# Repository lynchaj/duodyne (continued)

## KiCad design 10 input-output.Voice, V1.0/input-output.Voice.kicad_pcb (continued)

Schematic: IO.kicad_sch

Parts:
RN3: 10K; R_Array_SIP9
SW3: IO PORT ADDR; PinHeader_2x05_P2.54mm_Vertical
U25: 74LS688; DIP-20_W7.62mm_Socket

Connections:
GND: U25.10 (GND); also elsewhere on the board
unnamed: RN3.2 (R1), SW3.1, U25.18 (R7)
unnamed: RN3.3 (R2), SW3.3, U25.16 (R6)
unnamed: RN3.4 (R3), SW3.5, U25.14 (R5)
unnamed: RN3.5 (R4), SW3.7, U25.12 (R4)
unnamed: RN3.6 (R5), SW3.9, U25.9 (R3)
unnamed: RN3.9 (R8), U25.3 (R0), U25.4 (P1), U25.5 (R1), U25.6 (P2), U25.7 (R2)
VCC: RN3.1 (common), U25.20 (VCC); also elsewhere on the board
ZERO: SW3.2, SW3.4, SW3.6, SW3.8, SW3.10; also elsewhere on the board
bA3: U25.8 (P3); also elsewhere on the board
bA4: U25.11 (P4); also elsewhere on the board
bA5: U25.13 (P5); also elsewhere on the board
bA6: U25.15 (P6); also elsewhere on the board
bA7: U25.17 (P7); also elsewhere on the board
~BRD_SEL: U25.19 (P=R); also elsewhere on the board
~bIORQ: U25.1 (G); also elsewhere on the board
~bM1: U25.2 (P0); also elsewhere on the board

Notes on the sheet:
SET IO PORT
Note: IO Address Port $B8-$BF 1-2 =off - A7 (high) 3-4 =on - A6 (low) 5-6 =off - A5 (high) 7-8 =off - A4 (high) 9-10 =off - A3 (high)
IO SELECTION CIRCUIT TTS, ADC, DAC, SOUND
Note: Inhibit Board Operation During Interrupts ~{M1} = low, ~{IORQ} = low

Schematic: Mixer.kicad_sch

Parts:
C65, C66, C67, C68: 15p; C_Disc_D3.0mm_W1.6mm_P2.50mm
C69, C70, C71, C72, C73, C74, C75, C76, C77, C80, C81, C82, C83: 0.22u; C_Disc_D5.0mm_W2.5mm_P5.00mm
C78, C79: 100u; CP_Radial_D5.0mm_P2.50mm
J12: Headphone; Jack_3.5mm_PJ320E_Horizontal
JP3: AUD TTS; PinHeader_1x03_P2.54mm_Vertical
JP4: AUD LFT; PinHeader_1x03_P2.54mm_Vertical
JP5: AUD DAC; PinHeader_1x03_P2.54mm_Vertical
JP6: AUD RGT; PinHeader_1x03_P2.54mm_Vertical
JP7, JP8: SPK EN; PinHeader_1x02_P2.54mm_Vertical
LS1: Left Speaker; Jameco PCB Speaker 30mm 135722
LS2: Right Speaker; Jameco PCB Speaker 30mm 135722
R26, R27, R28, R29: 1M; R_Axial_DIN0207_L6.3mm_D2.5mm_P10.16mm_Horizontal
R30, R31, R32, R33: 47K; R_Axial_DIN0207_L6.3mm_D2.5mm_P10.16mm_Horizontal
R34, R35, R36, R37: 10K; R_Axial_DIN0207_L6.3mm_D2.5mm_P10.16mm_Horizontal
R38, R39, R40, R41: 100K; R_Axial_DIN0207_L6.3mm_D2.5mm_P10.16mm_Horizontal
RV2, RV3, RV4, RV5, RV6, RV7: 500K; Potentiometer_Bourns_3386P_Vertical
U27, U28: LM324; DIP-14_W7.62mm_Socket

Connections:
+12V: C79.1, R38.1, U27.4 (V+), U28.4 (V+); also elsewhere on the board
AUDIO_DAC: C71.2; also elsewhere on the board
AUDIO_SNL: C70.2; also elsewhere on the board
AUDIO_SNR: C72.2; also elsewhere on the board
AUDIO_TTS: C69.2; also elsewhere on the board
GND: C77.2, C78.2, C79.2, J12.S, JP3.3 (B), JP4.3 (B), JP5.3 (B), JP6.3 (B), LS1.2, LS2.2, R39.2, RV6.3, RV7.3, U27.11 (V-), U28.11 (V-); also elsewhere on the board
unnamed: C65.1, R26.1, R30.2, RV2.1, U27.2 (-)
unnamed: C65.2, C73.1, R26.2, RV2.2, RV2.3, U27.1
unnamed: C66.1, R27.1, R31.2, RV3.1, U27.6 (-)
unnamed: C66.2, C74.1, R27.2, RV3.2, RV3.3, U27.7
unnamed: C67.1, R28.1, R32.2, RV4.1, U28.2 (-)
unnamed: C67.2, C75.1, R28.2, RV4.2, RV4.3, U28.1
unnamed: C68.1, R29.1, R33.2, RV5.1, U28.6 (-)
unnamed: C68.2, C76.1, R29.2, RV5.2, RV5.3, U28.7
unnamed: C69.1, R30.1
unnamed: C70.1, R31.1
unnamed: C71.1, R32.1
unnamed: C72.1, R33.1
unnamed: C73.2, R34.1
unnamed: C74.2, R35.1
unnamed: C75.2, R36.1
unnamed: C76.2, R37.1
unnamed: C80.1, JP3.2 (C), JP4.2 (C), R40.1, U27.9 (-)
unnamed: C80.2, C82.1, R40.2, U27.8
unnamed: C81.1, JP5.2 (C), JP6.2 (C), R41.1, U28.9 (-)
unnamed: C81.2, C83.1, R41.2, U28.8
unnamed: C82.2, RV6.1
unnamed: C83.2, RV7.1
unnamed: J12.R1, JP8.1 (A), RV7.2
unnamed: J12.T, JP7.1 (A), RV6.2
unnamed: JP3.1 (A), R34.2
unnamed: JP4.1 (A), R35.2
unnamed: JP5.1 (A), R36.2
unnamed: JP6.1 (A), R37.2
unnamed: JP7.2 (B), LS1.1
unnamed: JP8.2 (B), LS2.1
VB: C77.1, C78.1, R38.2, R39.1, U27.3 (+), U27.5 (+), U27.10 (+), U28.3 (+), U28.5 (+), U28.10 (+); also elsewhere on the board

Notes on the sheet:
NOTE: HEADPHONE JACK 3.5 mm Audio Jack Connector PCB Product Name: WQP-PJ320E WQP-PJ320E is a 3.5mm audio jack, DIP type, right angle.

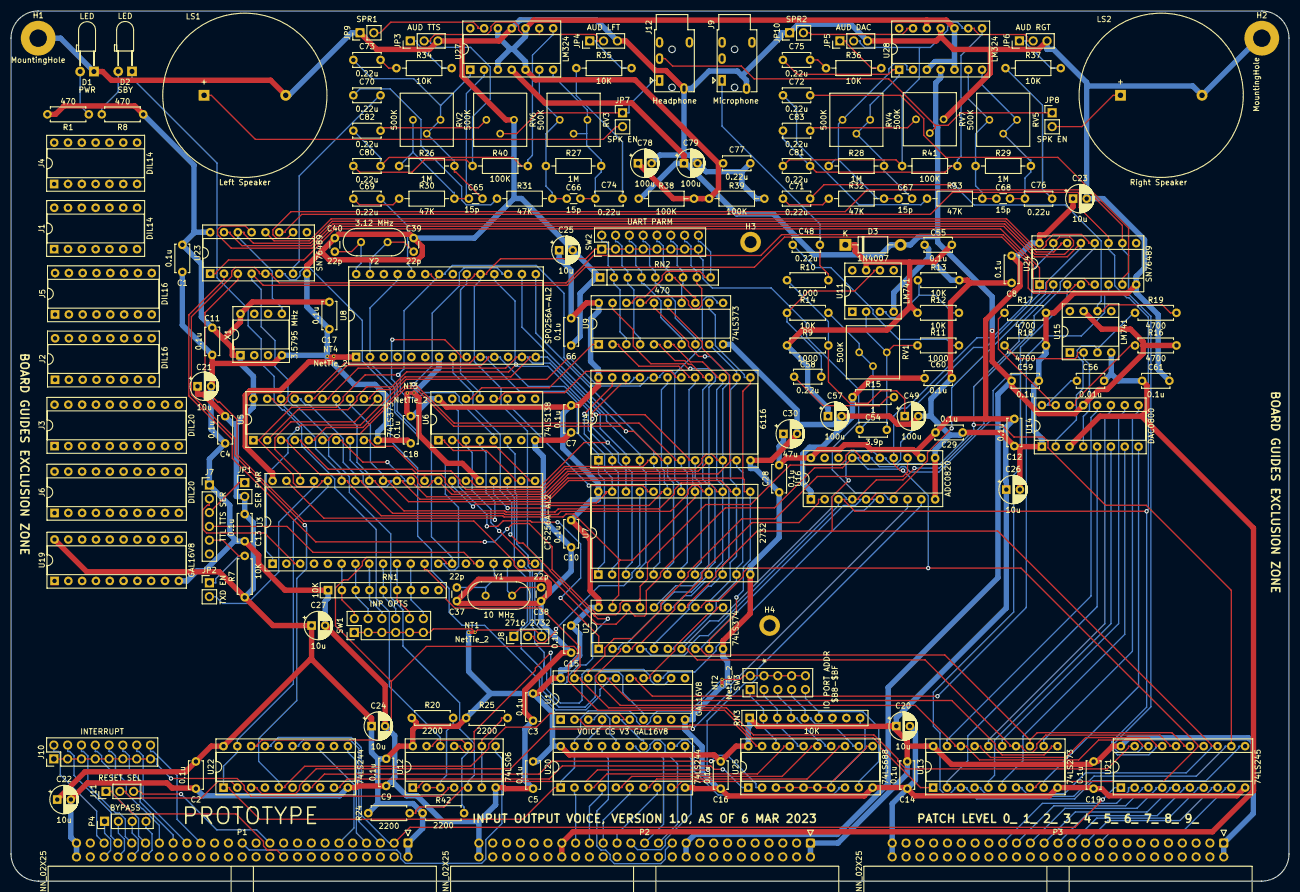
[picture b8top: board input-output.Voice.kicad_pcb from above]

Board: 2 copper layers, 235.0 x 160.0 mm, 176 parts (0 on the bottom side), 208 nets.

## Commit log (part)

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2023-04-01 more KiCAD 6 transition clean up Signed-off-by: lynchaj <lynchaj@yahoo.com>
2023-04-05 IO port update and clean-ups Signed-off-by: lynchaj <lynchaj@yahoo.com>
2023-08-01 Create initial build and test
2023-08-01 Update initial build and test
2023-08-06 Add Dual32V1.0
2023-08-19 ESP32 work
2023-08-20 new test program
2023-08-21 esp test program work
2023-08-21 esp test work and bug fix to serial 2 firmware
2023-08-23 Update !initial build and test
2023-08-28 ESP32 reset
2023-09-02 Add 65816 Processor board
2023-09-02 espconf utility
2023-09-02 correct outgoing connection issue
2023-09-05 update ESP32 with common serial format
2023-09-15 FIX SERIAL FIRMWARE ISSUE
2023-10-02 65c816 work
2023-10-12 add TMS9995
2023-10-15 tms9995 work
2023-10-15 tms9995
2023-10-31 tms9995 updates
2023-11-12 TMS9995 patches
2023-11-13 Interrupt updates for 65816 and TMS9995
2023-12-11 65816 updates
2023-12-16 TMS9994 updates
2023-12-29 Add 6809 processor
2023-12-29 6809 fixes
2023-12-30 TMS updates, add CF Image
2023-12-31 6809 updates
2023-12-31 TMS9995 documentation updates
2024-01-06 65816 GAL updates;
2024-01-08 TMS software added
2024-01-15 6809 patches
2024-01-15 6809 work
2024-01-20 IO GAL update for TMS9995
2024-01-21 6809 GAL update
2024-01-22 6809 documentation update
2024-02-05 restore missing files
2024-04-14 Front panel 1.1 firmware
2024-05-05 readme update
2024-05-09 FIRQ 6809 fix
2024-05-12 Initial commit of DACTONE program.
    This program generates a sine wave of a specified
    frequencies and sends the samples to the DAC.
2024-05-12 Add DACTONE.COM binary.
2024-05-12 Update the README.md file.
2024-05-12 More README updates.
2024-05-12 update documentation
2024-05-14 65816 update
2024-06-23 65816 and 6809 updates
2024-07-06 add 80c188 board
2024-07-20 80c188 work
2024-09-08 PCB work
2024-09-15 80c188 updates
2024-10-21 80c188 working, monitor work
2024-10-21 monitor work
2024-10-28 working design 80c188
2024-10-28 add new backplane
2024-11-03 80c188 source cleanup
2024-11-03 update docs
2024-11-04 80c188 pcb updates
2024-11-24 BIOS updates
2024-12-08 support duodyne media board on 80c188
2024-12-08 support duodyne multi io board on 80c188
2024-12-09 Add MultiIO support for 80C188
2024-12-09 add disable flag for 8242 on 80c188
2024-12-15 remove memory mapped video board
2025-04-06 Add alternate front panel
